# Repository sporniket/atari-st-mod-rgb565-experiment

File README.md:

# An experimental extended palette for the Atari ST

By David SPORN
Creative Commons CC0

more information later...

See `32768-colors.md` for the original description by Barry Orlando.

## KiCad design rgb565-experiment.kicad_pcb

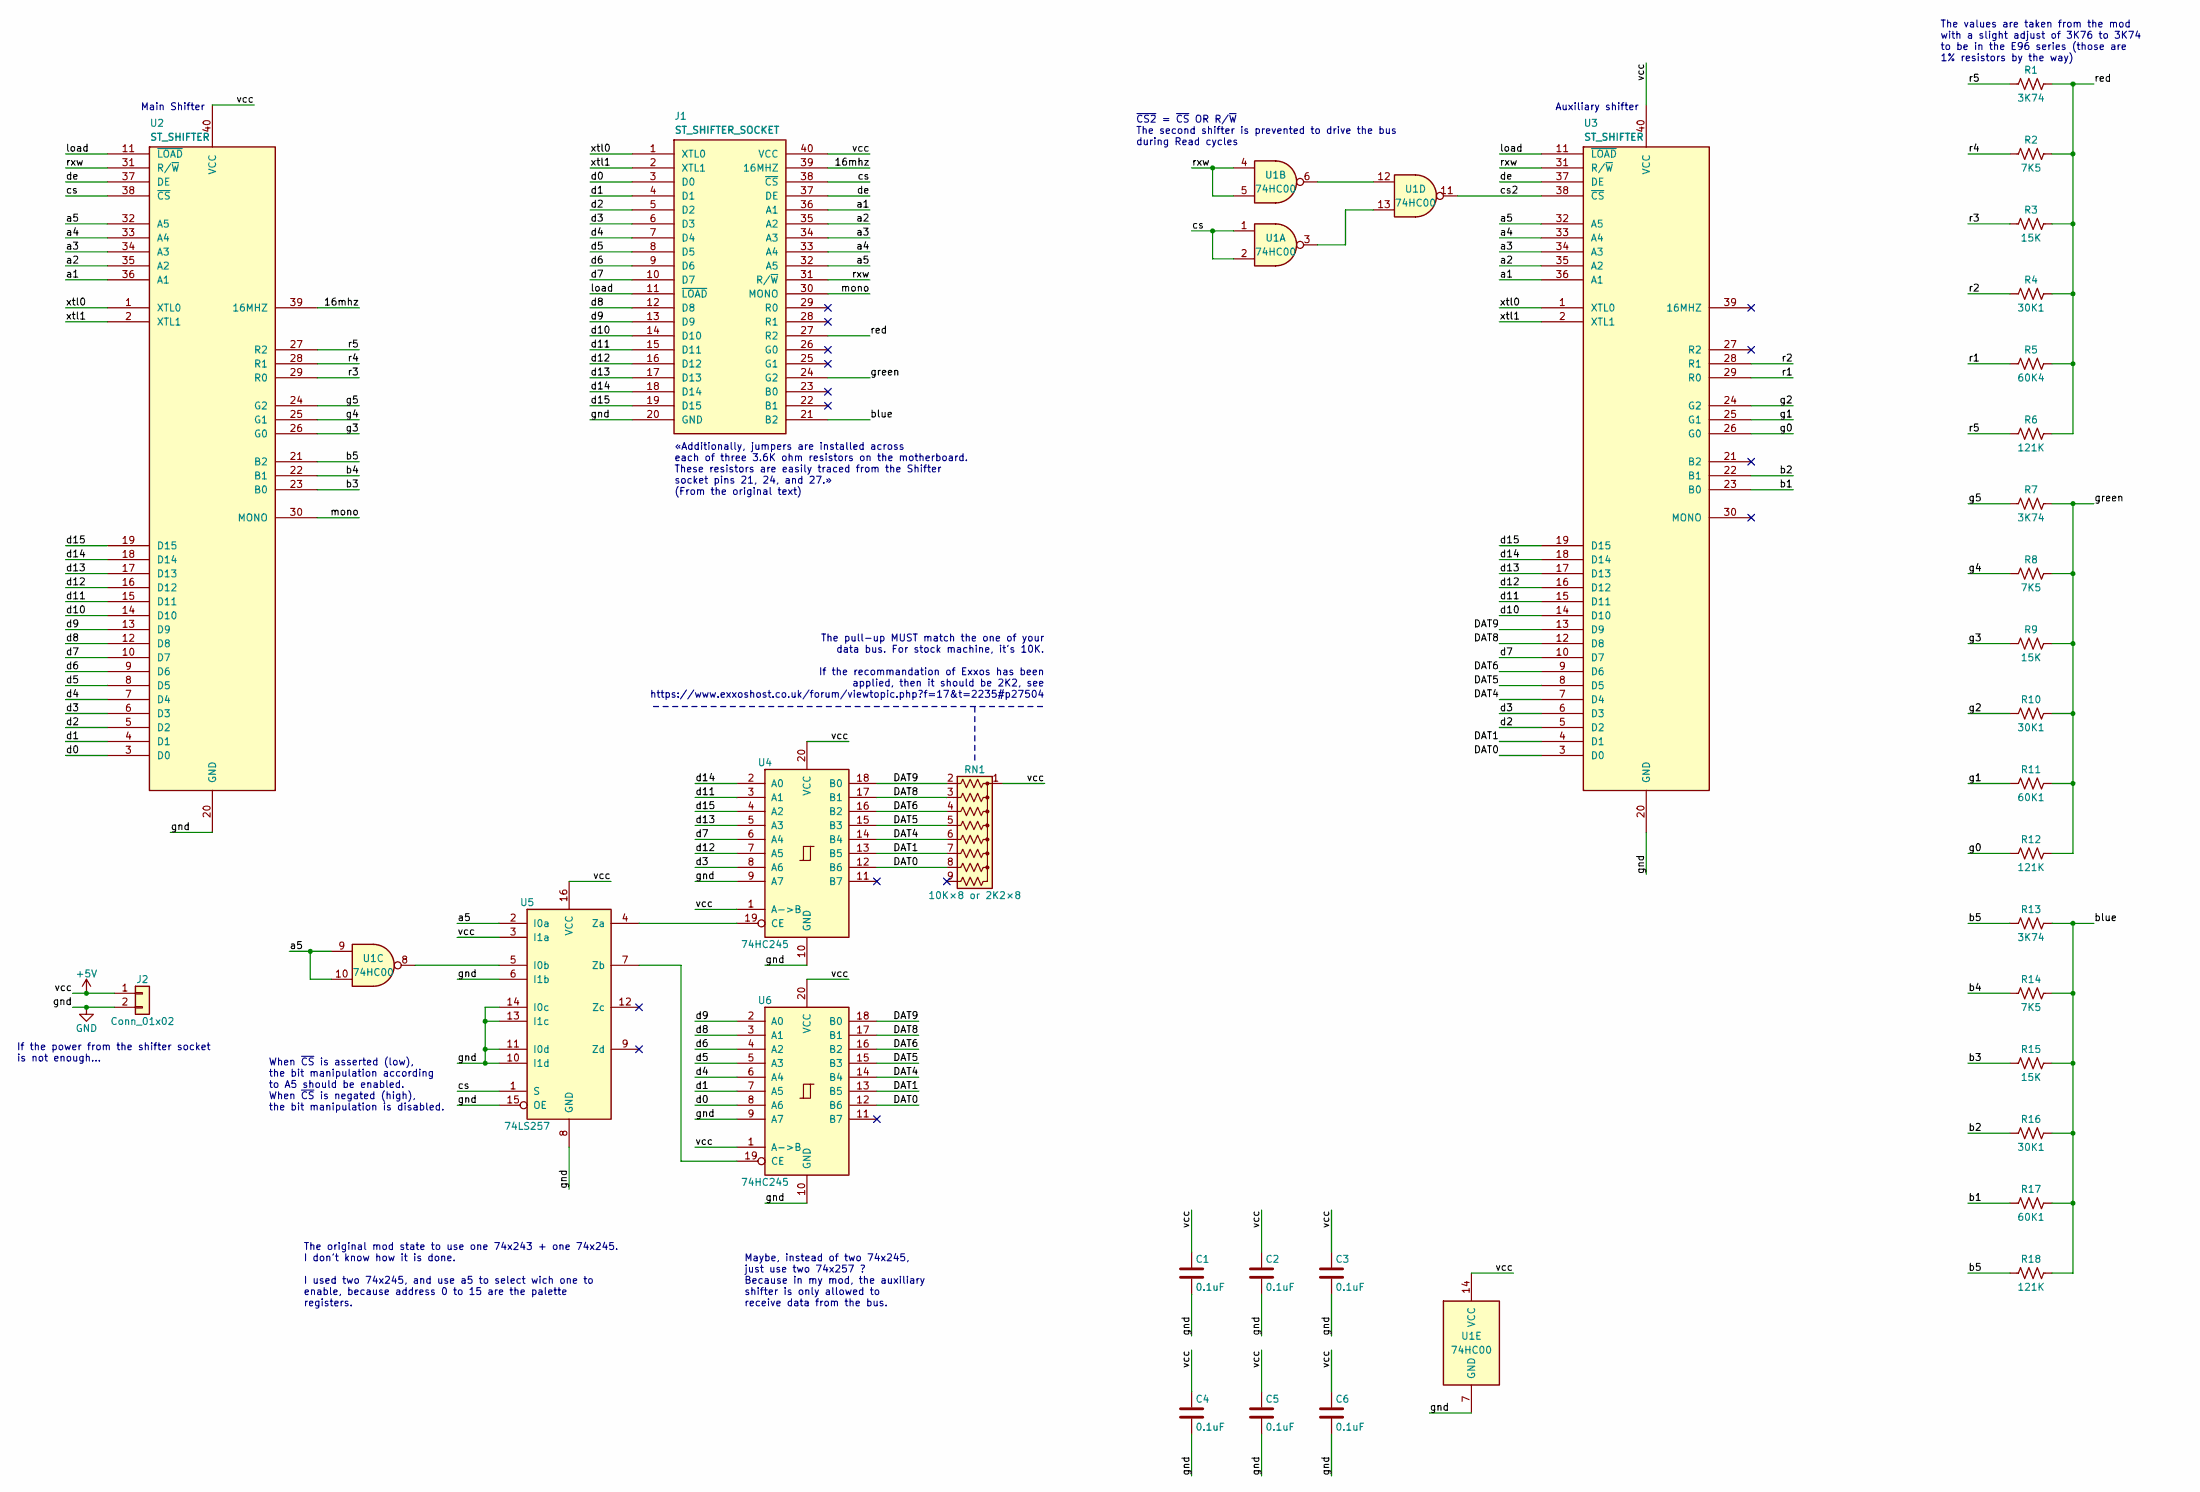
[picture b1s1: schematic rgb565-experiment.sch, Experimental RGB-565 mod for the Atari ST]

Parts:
C1, C2, C3, C4, C5, C6: 0.1uF; Passive_THT_capacitor_mlcc_W2.54mm_L7.62mm
J1: ST_SHIFTER_SOCKET; DIP-40_W15.24mm_Socket
J2: Conn_01x02; PinHeader_1x02_P2.54mm_Vertical
R1, R7, R13: 3K74; Passive_THT_resistor_W2.54mm_L10.16mm
R2, R8, R14: 7K5; Passive_THT_resistor_W2.54mm_L10.16mm
R3, R9, R15: 15K; Passive_THT_resistor_W2.54mm_L10.16mm
R4, R10, R16: 30K1; Passive_THT_resistor_W2.54mm_L10.16mm
R5: 60K4; Passive_THT_resistor_W2.54mm_L10.16mm
R6, R12, R18: 121K; Passive_THT_resistor_W2.54mm_L10.16mm
R11, R17: 60K1; Passive_THT_resistor_W2.54mm_L10.16mm
RN1: 10K×8 or 2K2×8; R_Array_SIP9
U1: 74HC00; DIP-14_W7.62mm_Socket
U2, U3: ST_SHIFTER; DIP-40_W15.24mm_Socket
U4, U6: 74HC245; DIP-20_W7.62mm_Socket
U5: 74LS257; DIP-16_W7.62mm_Socket

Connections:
+5V: C1.1, C2.1, C3.1, C4.1, C5.1, C6.1, J1.40 (VCC), J2.1, RN1.1 (common), U1.14 (VCC), U2.40 (VCC), U3.40 (VCC), U4.1 (A->B), U4.20 (VCC), U5.3 (I1a), U5.16 (VCC), U6.1 (A->B), U6.20 (VCC)
/16mhz: J1.39 (16MHZ), U2.39 (16MHZ)
/DAT0: RN1.8 (R7), U3.3 (D0), U4.12 (B6), U6.12 (B6)
/DAT1: RN1.7 (R6), U3.4 (D1), U4.13 (B5), U6.13 (B5)
/DAT4: RN1.6 (R5), U3.7 (D4), U4.14 (B4), U6.14 (B4)
/DAT5: RN1.5 (R4), U3.8 (D5), U4.15 (B3), U6.15 (B3)
/DAT6: RN1.4 (R3), U3.9 (D6), U4.16 (B2), U6.16 (B2)
/DAT8: RN1.3 (R2), U3.12 (D8), U4.17 (B1), U6.17 (B1)
/DAT9: RN1.2 (R1), U3.13 (D9), U4.18 (B0), U6.18 (B0)
/a1: J1.36 (A1), U2.36 (A1), U3.36 (A1)
/a2: J1.35 (A2), U2.35 (A2), U3.35 (A2)
/a3: J1.34 (A3), U2.34 (A3), U3.34 (A3)
/a4: J1.33 (A4), U2.33 (A4), U3.33 (A4)
/a5: J1.32 (A5), U1.9, U1.10, U2.32 (A5), U3.32 (A5), U5.2 (I0a)
/b1: R17.1, U3.23 (B0)
/b2: R16.1, U3.22 (B1)
/b3: R15.1, U2.23 (B0)
/b4: R14.1, U2.22 (B1)
/b5: R13.1, R18.1, U2.21 (B2)
/blue: J1.21 (B2), R13.2, R14.2, R15.2, R16.2, R17.2, R18.2
/cs: J1.38 (~CS~), U1.1, U1.2, U2.38 (~CS~), U5.1 (S)
/cs2: U1.11, U3.38 (~CS~)
/d0: J1.3 (D0), U2.3 (D0), U6.8 (A6)
/d1: J1.4 (D1), U2.4 (D1), U6.7 (A5)
/d2: J1.5 (D2), U2.5 (D2), U3.5 (D2)
/d3: J1.6 (D3), U2.6 (D3), U3.6 (D3), U4.8 (A6)
/d4: J1.7 (D4), U2.7 (D4), U6.6 (A4)
/d5: J1.8 (D5), U2.8 (D5), U6.5 (A3)
/d6: J1.9 (D6), U2.9 (D6), U6.4 (A2)
/d7: J1.10 (D7), U2.10 (D7), U3.10 (D7), U4.6 (A4)
/d8: J1.12 (D8), U2.12 (D8), U6.3 (A1)
/d9: J1.13 (D9), U2.13 (D9), U6.2 (A0)
/d10: J1.14 (D10), U2.14 (D10), U3.14 (D10)
/d11: J1.15 (D11), U2.15 (D11), U3.15 (D11), U4.3 (A1)
/d12: J1.16 (D12), U2.16 (D12), U3.16 (D12), U4.7 (A5)
/d13: J1.17 (D13), U2.17 (D13), U3.17 (D13), U4.5 (A3)
/d14: J1.18 (D14), U2.18 (D14), U3.18 (D14), U4.2 (A0)
/d15: J1.19 (D15), U2.19 (D15), U3.19 (D15), U4.4 (A2)
/de: J1.37 (DE), U2.37 (DE), U3.37 (DE)
/g0: R12.1, U3.26 (G0)
/g1: R11.1, U3.25 (G1)
/g2: R10.1, U3.24 (G2)
/g3: R9.1, U2.26 (G0)
/g4: R8.1, U2.25 (G1)
/g5: R7.1, U2.24 (G2)
/green: J1.24 (G2), R7.2, R8.2, R9.2, R10.2, R11.2, R12.2
/load: J1.11 (~LOAD~), U2.11 (~LOAD~), U3.11 (~LOAD~)
/mono: J1.30 (MONO), U2.30 (MONO)
/r1: R5.1, U3.29 (R0)
/r2: R4.1, U3.28 (R1)
/r3: R3.1, U2.29 (R0)
/r4: R2.1, U2.28 (R1)
/r5: R1.1, R6.1, U2.27 (R2)
/red: J1.27 (R2), R1.2, R2.2, R3.2, R4.2, R5.2, R6.2
/rxw: J1.31 (R/~W~), U1.4, U1.5, U2.31 (R/~W~), U3.31 (R/~W~)
/xtl0: J1.1 (XTL0), U2.1 (XTL0), U3.1 (XTL0)
/xtl1: J1.2 (XTL1), U2.2 (XTL1), U3.2 (XTL1)
GND: C1.2, C2.2, C3.2, C4.2, C5.2, C6.2, J1.20 (GND), J2.2, U1.7 (GND), U2.20 (GND), U3.20 (GND), U4.9 (A7), U4.10 (GND), U5.6 (I1b), U5.8 (GND), U5.10 (I1d), U5.11 (I0d), U5.13 (I1c), U5.14 (I0c), U5.15 (OE), U6.9 (A7), U6.10 (GND)
unnamed: U1.8, U5.5 (I0b)
unnamed: U1.6, U1.12
unnamed: U1.3, U1.13
unnamed: U4.19 (CE), U5.4 (Za)
unnamed: U5.7 (Zb), U6.19 (CE)

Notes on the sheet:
~CS2~ = ~CS~ OR R/~W~ The second shifter is prevented to drive the bus during Read cycles
The original mod state to use one 74x243 + one 74x245. I don't know how it is done. I used two 74x245, and use a5 to select wich one to enable, because address 0 to 15 are the palette registers.
When ~CS~ is asserted (low), the bit manipulation according to A5 should be enabled. When ~CS~ is negated (high), the bit manipulation is disabled.
Maybe, instead of two 74x245, just use two 74x257 ? Because in my mod, the auxiliary shifter is only allowed to receive data from the bus.
Main Shifter
Auxiliary shifter
«Additionally, jumpers are installed across each of three 3.6K ohm resistors on the motherboard. These resistors are easily traced from the Shifter socket pins 21, 24, and 27.» (From the original text)
The values are taken from the mod with a slight adjust of 3K76 to 3K74 to be in the E96 series (those are 1% resistors by the way)
If the power from the shifter socket is not enough...
The pull-up MUST match the one of your data bus. For stock machine, it's 10K. If the recommandation of Exxos has been applied, then it should be 2K2, see https://www.exxoshost.co.uk/forum/viewtopic.php?f=17&t=2235#p27504

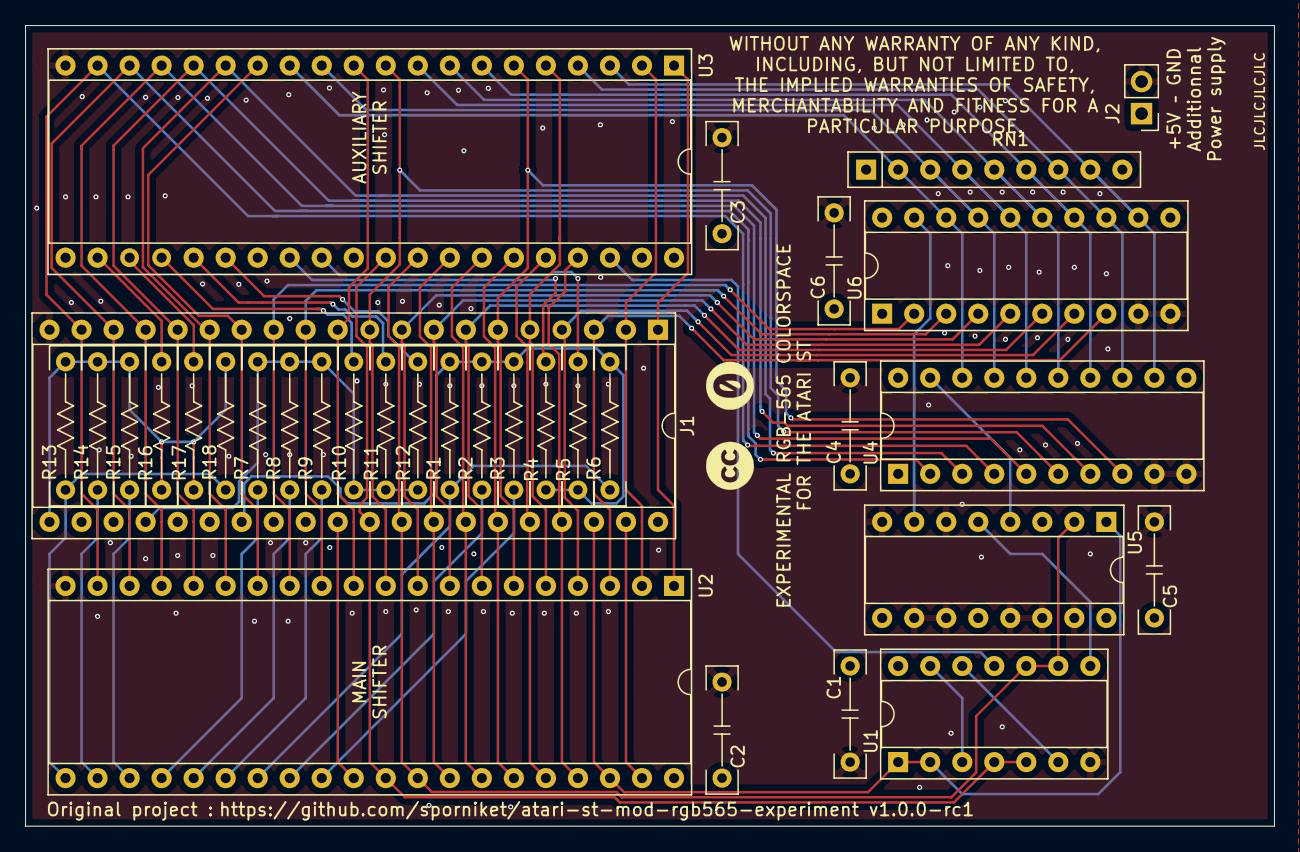
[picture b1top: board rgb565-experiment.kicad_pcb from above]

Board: 4 copper layers, 99.1 x 63.5 mm, 33 parts (0 on the bottom side), 63 nets.

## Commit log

2021-12-14 Initial draft
2021-12-15 schematic complete with color dac
2021-12-15 prepare public work
2021-12-15 include original mod description
2021-12-15 update submodule
2021-12-15 fixes some ERC warning
2021-12-15 tweaked schematics arrangement
2021-12-16 fixed typo of formatting of the original text
2021-12-16 fixed the resistor values to match the original mod
2021-12-16 add additionnal connectors : supplemental power, digital 18bits signal
2021-12-16 assign footprints
2021-12-17 added pull-up for data, removed redundant connector to digital signal, continue tracing
2021-12-17 almost done routing
2021-12-18 done initial routing
2021-12-18 done DRC checks
2021-12-18 copper pouring all over the faces
2021-12-18 additionnal mentions
2021-12-18 version 1 experience candidate 1
2021-12-22 Adjust width to be a bit narrower
2021-12-24 shaving a little bit of length beside shifter sockets
2021-12-24 connected some bits of copper pour
2021-12-24 prepare next version
2022-04-30 Release Candidate 1 : modifications following experiments with the experimental version
